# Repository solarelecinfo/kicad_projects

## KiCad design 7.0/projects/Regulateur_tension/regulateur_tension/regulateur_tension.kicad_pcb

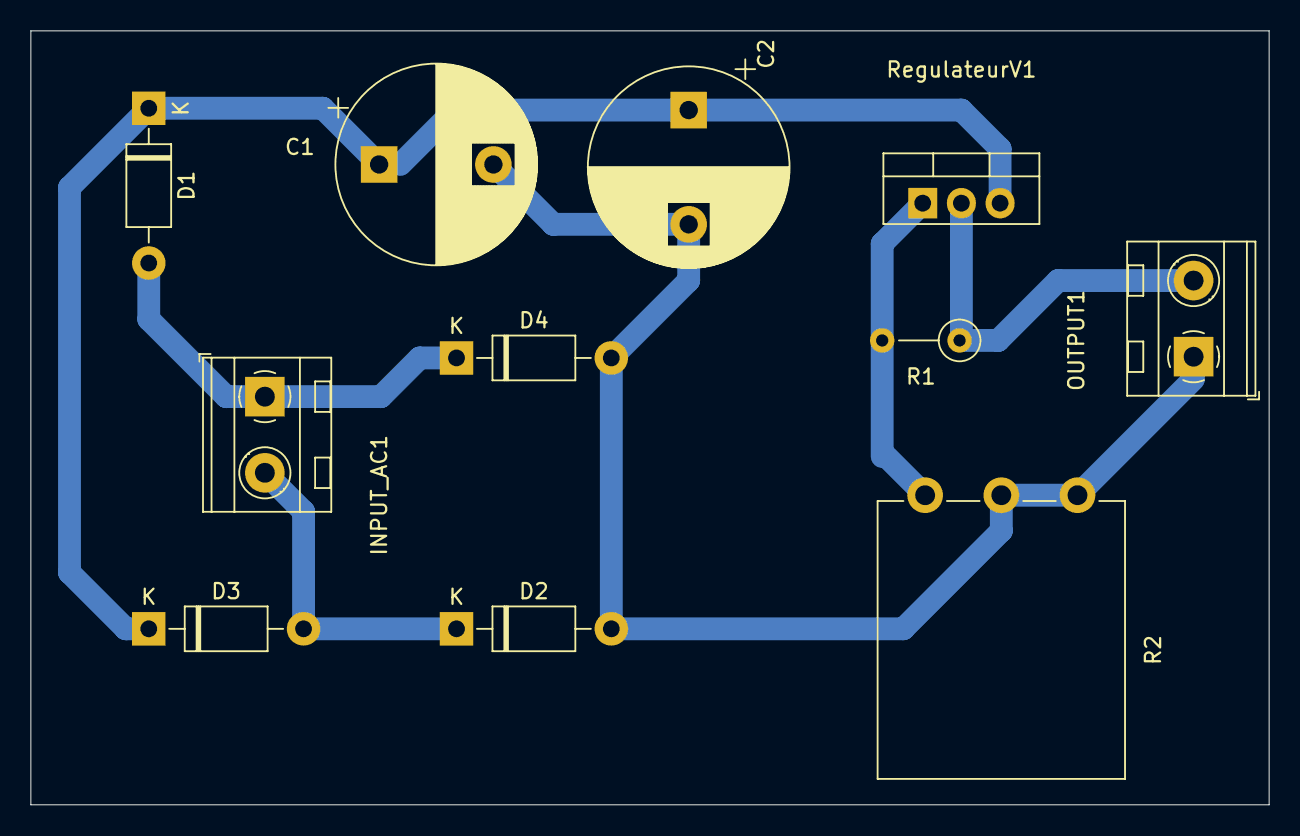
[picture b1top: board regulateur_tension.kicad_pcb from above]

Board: 2 copper layers, 81.3 x 50.8 mm, 11 parts (0 on the bottom side), 6 nets.

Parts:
C1, C2: 1000μF; CP_Radial_D13.0mm_P7.50mm
D1, D2, D3, D4: 1N4007; D_DO-41_SOD81_P10.16mm_Horizontal
INPUT_AC1: IN_AC; TerminalBlock_MetzConnect_Type094_RT03502HBLU_1x02_P5.00mm_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
OUTPUT1: OUT_DC; TerminalBlock_MetzConnect_Type094_RT03502HBLU_1x02_P5.00mm_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
R1: 220; R_Axial_DIN0207_L6.3mm_D2.5mm_P5.08mm_Vertical
R2: 654; Potentiometer_Piher_PC-16_Single_Vertical
RegulateurV1: LM317_TO-220; TO-220-3_Vertical

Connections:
GND: C1.2, C2.2, D2.2 (A), D4.2 (A), OUTPUT1.1, R2.2, R2.3
unnamed: D1.2 (A), D4.1 (K), INPUT_AC1.1
unnamed: C1.1, C2.1, D1.1 (K), D3.1 (K), RegulateurV1.3 (VI)
unnamed: D2.1 (K), D3.2 (A), INPUT_AC1.2
unnamed: OUTPUT1.2, R1.1, RegulateurV1.2 (VO)
unnamed: R1.2, R2.1, RegulateurV1.1 (ADJ)

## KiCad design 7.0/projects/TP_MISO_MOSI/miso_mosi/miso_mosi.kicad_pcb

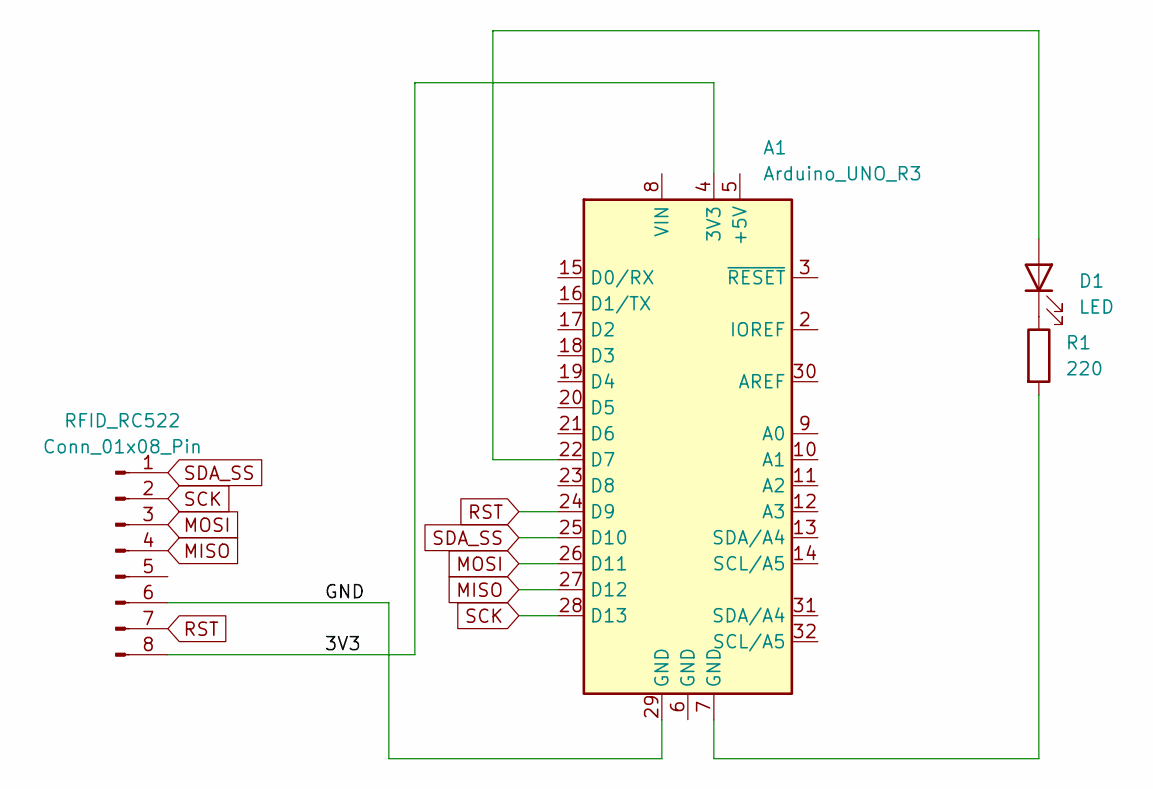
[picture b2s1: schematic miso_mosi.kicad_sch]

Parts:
A1: Arduino_UNO_R3
D1: LED; LED_D3.0mm_Horizontal_O3.81mm_Z2.0mm
R1: 220; R_Axial_DIN0614_L14.3mm_D5.7mm_P25.40mm_Horizontal
RFID_RC522: Conn_01x08_Pin; PinHeader_1x08_P2.54mm_Horizontal

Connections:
/3V3: A1.4 (3V3), RFID_RC522.8
/GND: A1.29 (GND), RFID_RC522.6
MISO: A1.27 (D12), RFID_RC522.4
MOSI: A1.26 (D11), RFID_RC522.3
unnamed: A1.22 (D7), D1.2 (A)
unnamed: A1.7 (GND), R1.2
unnamed: D1.1 (K), R1.1
RST: A1.24 (D9), RFID_RC522.7
SCK: A1.28 (D13), RFID_RC522.2
SDA_SS: A1.25 (D10), RFID_RC522.1

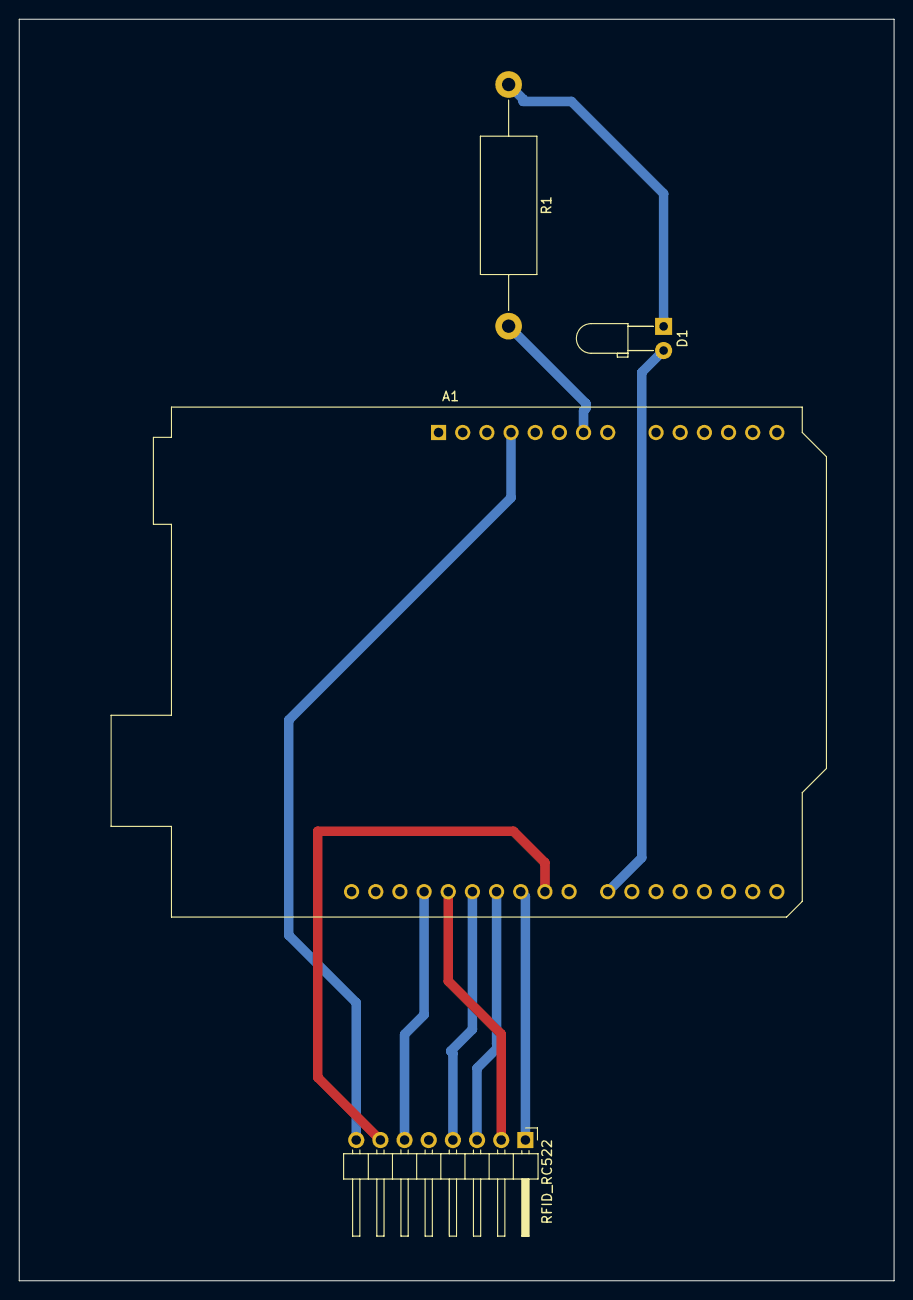
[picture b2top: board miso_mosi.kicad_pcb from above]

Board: 2 copper layers, 91.9 x 132.6 mm, 4 parts (0 on the bottom side), 10 nets.

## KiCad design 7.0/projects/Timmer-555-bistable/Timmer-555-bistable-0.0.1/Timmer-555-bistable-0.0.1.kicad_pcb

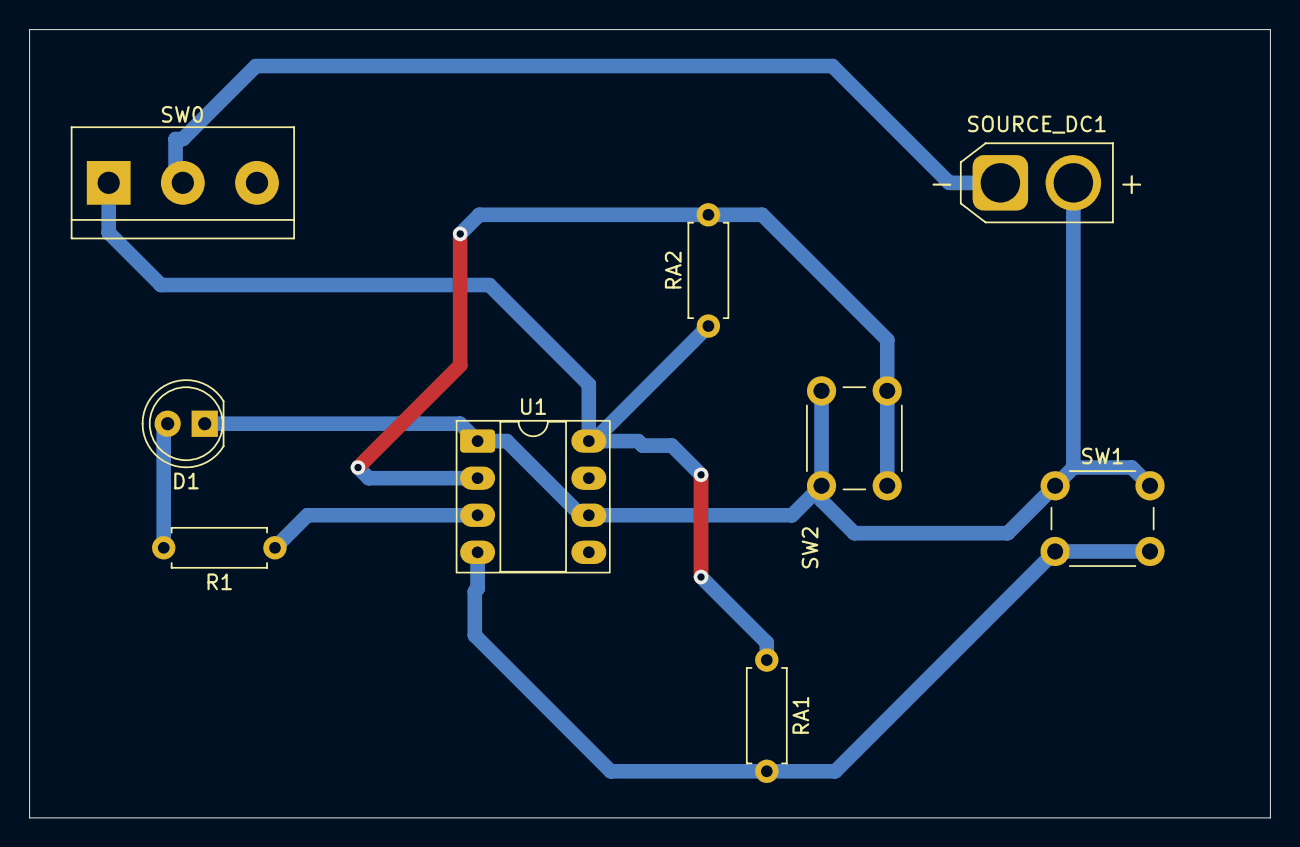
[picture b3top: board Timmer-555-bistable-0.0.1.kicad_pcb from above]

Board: 2 copper layers, 85.0 x 54.0 mm, 9 parts (0 on the bottom side), 7 nets.

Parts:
D1: LED; LED_D5.0mm
R1: 220; R_Axial_DIN0207_L6.3mm_D2.5mm_P7.62mm_Horizontal
RA1, RA2: 10k; R_Axial_DIN0207_L6.3mm_D2.5mm_P7.62mm_Horizontal
SOURCE_DC1: 5; AMASS_XT30U-M_1x02_P5.0mm_Vertical
SW0: SW_SWITCH; TerminalBlock_bornier-3_P5.08mm
SW1, SW2: SW_Push; SW_PUSH_6mm_H5mm
U1: LM555xM; DIP-8_W7.62mm_Socket_LongPads

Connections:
unnamed: D1.2 (A), R1.2
unnamed: SOURCE_DC1.1, SW0.2 (B)
unnamed: RA1.1, RA2.1, SW0.1 (C), U1.8 (VCC)
unnamed: R1.1, U1.3 (Q)
unnamed: RA1.2, SW1.2, U1.4 (R)
THR: D1.1 (K), SOURCE_DC1.2, SW1.1, SW2.1, U1.1 (GND), U1.6 (THR)
TRG: RA2.2, SW2.2, U1.2 (TR)

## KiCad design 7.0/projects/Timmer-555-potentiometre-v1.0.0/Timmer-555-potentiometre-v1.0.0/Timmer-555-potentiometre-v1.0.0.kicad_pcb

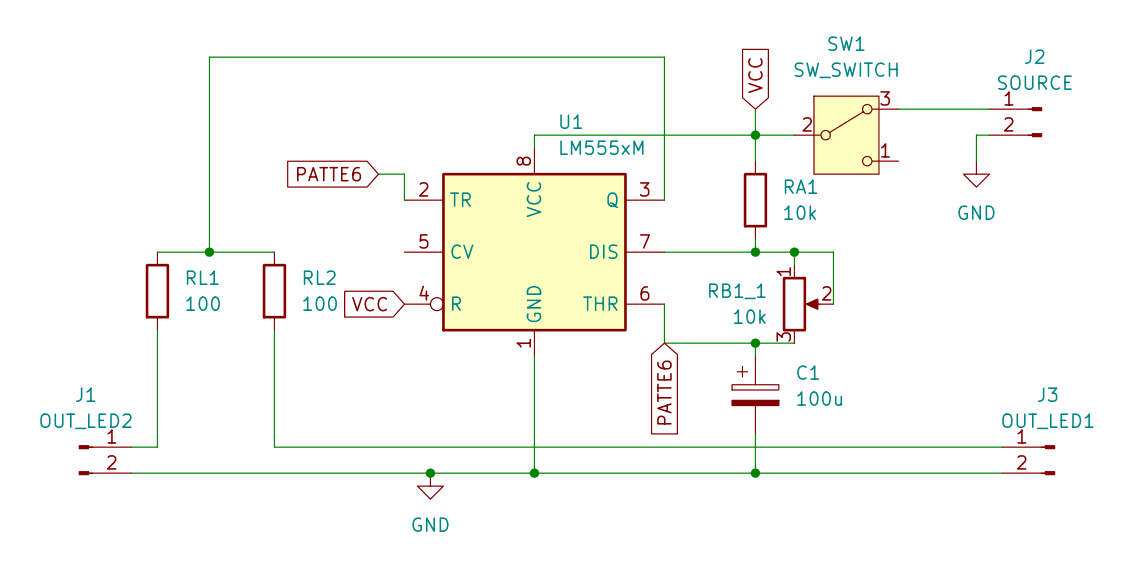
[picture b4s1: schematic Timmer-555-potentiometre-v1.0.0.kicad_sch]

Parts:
C1: 100u; CP_Radial_D8.0mm_P5.00mm
J1: OUT_LED2; TerminalBlock_MetzConnect_Type094_RT03502HBLU_1x02_P5.00mm_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
J2: SOURCE; TerminalBlock_MetzConnect_Type094_RT03502HBLU_1x02_P5.00mm_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
J3: OUT_LED1; TerminalBlock_MetzConnect_Type094_RT03502HBLU_1x02_P5.00mm_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
RA1: 10k; R_Axial_DIN0207_L6.3mm_D2.5mm_P7.62mm_Horizontal
RB1_1: 10k; TerminalBlock_bornier-3_P5.08mm
RL1, RL2: 100; R_Axial_DIN0207_L6.3mm_D2.5mm_P7.62mm_Horizontal
SW1: SW_SWITCH; TerminalBlock_bornier-3_P5.08mm
U1: LM555xM; DIP-8_W7.62mm_Socket_LongPads

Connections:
GND: C1.2, J1.2, J2.2, J3.2, U1.1 (GND)
unnamed: J1.1, RL1.2
unnamed: J2.1, SW1.3 (A)
unnamed: J3.1, RL2.2
unnamed: RA1.2, RB1_1.1, RB1_1.2, U1.7 (DIS)
unnamed: RL1.1, RL2.1, U1.3 (Q)
PATTE6: C1.1, RB1_1.3, U1.2 (TR), U1.6 (THR)
VCC: RA1.1, SW1.2 (B), U1.4 (R), U1.8 (VCC)

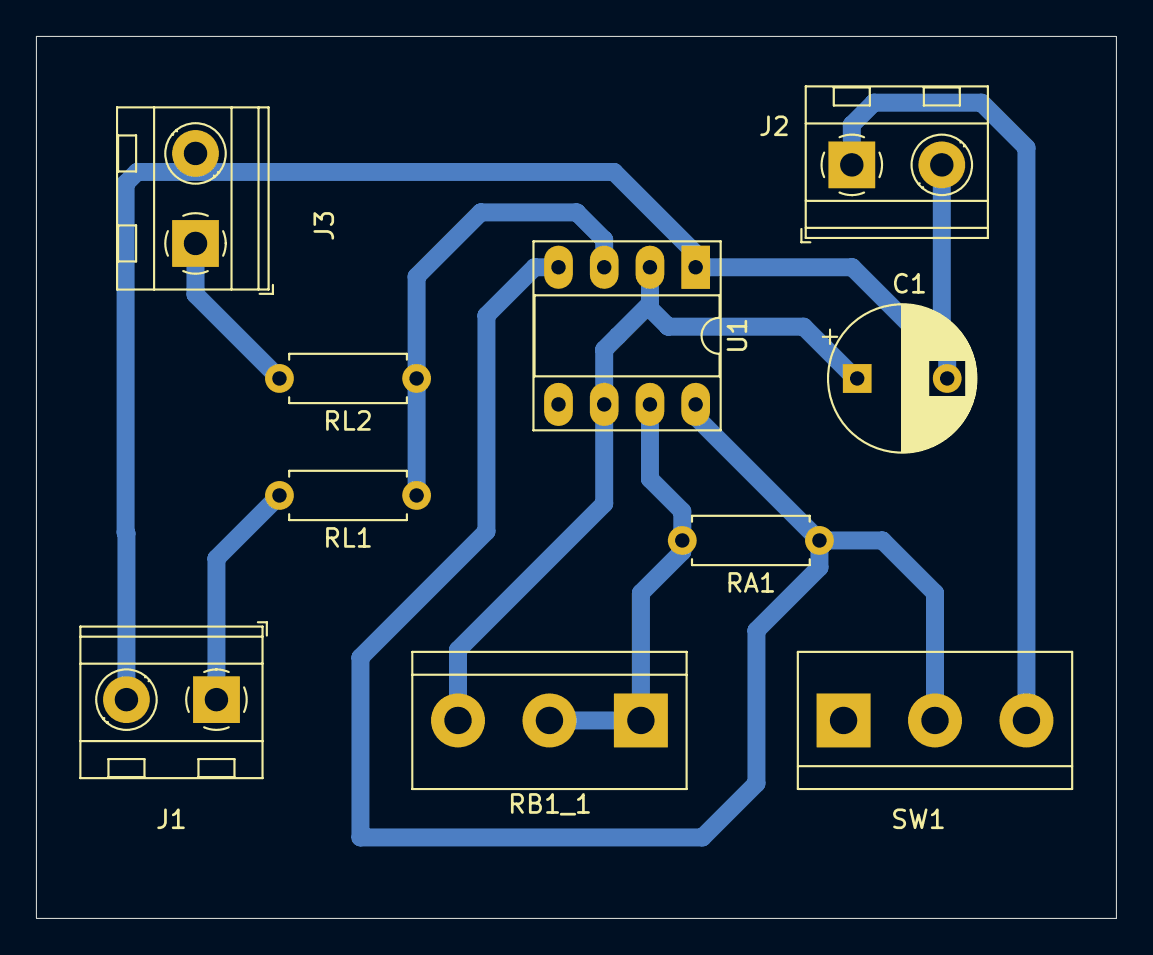
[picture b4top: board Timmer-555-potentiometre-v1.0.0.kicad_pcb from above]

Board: 2 copper layers, 60.0 x 49.0 mm, 10 parts (0 on the bottom side), 8 nets.
